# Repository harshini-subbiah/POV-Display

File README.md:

#  POV-Display
Persistence of Vision (POV) is an optical phenomenon where an image remains on the retina for a short time even after the object is no longer visible.
This project implements a POV Display using an Arduino Nano and a rotating set of LEDs. By leveraging the phenomenon where an image remains on the retina for ~1/16th of a second, it creates the illusion of characters or symbols floating in the air.

---
#  Hardware Required
Arduino Nano

1000 RPM DC Motor

5mm Red LEDs

220Ω Resistors

1K Ω Resistors

2K Ω Resistors

IR Sensor

Bluetooth Module (HC-05)

12V Battery

9V Battery

General Purpose Board

Jumper Wires

Hylam Sheet

Zip Ties

Soldering Iron & Wire

---
#  Software Required
1.Arduino IDE to run Code.ino file

2.Serial Bluetooth Terminal app for Bluetooth module

---
#  Setup
1.Follow the circuit diagram and make the proper connections of all the components.

2.Load the Code.ino file to the Nano.

3.Connect the Bluetooth module to the app. It will appear as HC-05 and the password will either be 1234 or 0000.

---
# Circuit Diagram

---

#  Contributors
1. S Harini 

2. Kiran Sampath 

3. Krithikesh

---
# Mentors
1. Mr.Suresh Sir
2. Mr.Vijaykumar Sir

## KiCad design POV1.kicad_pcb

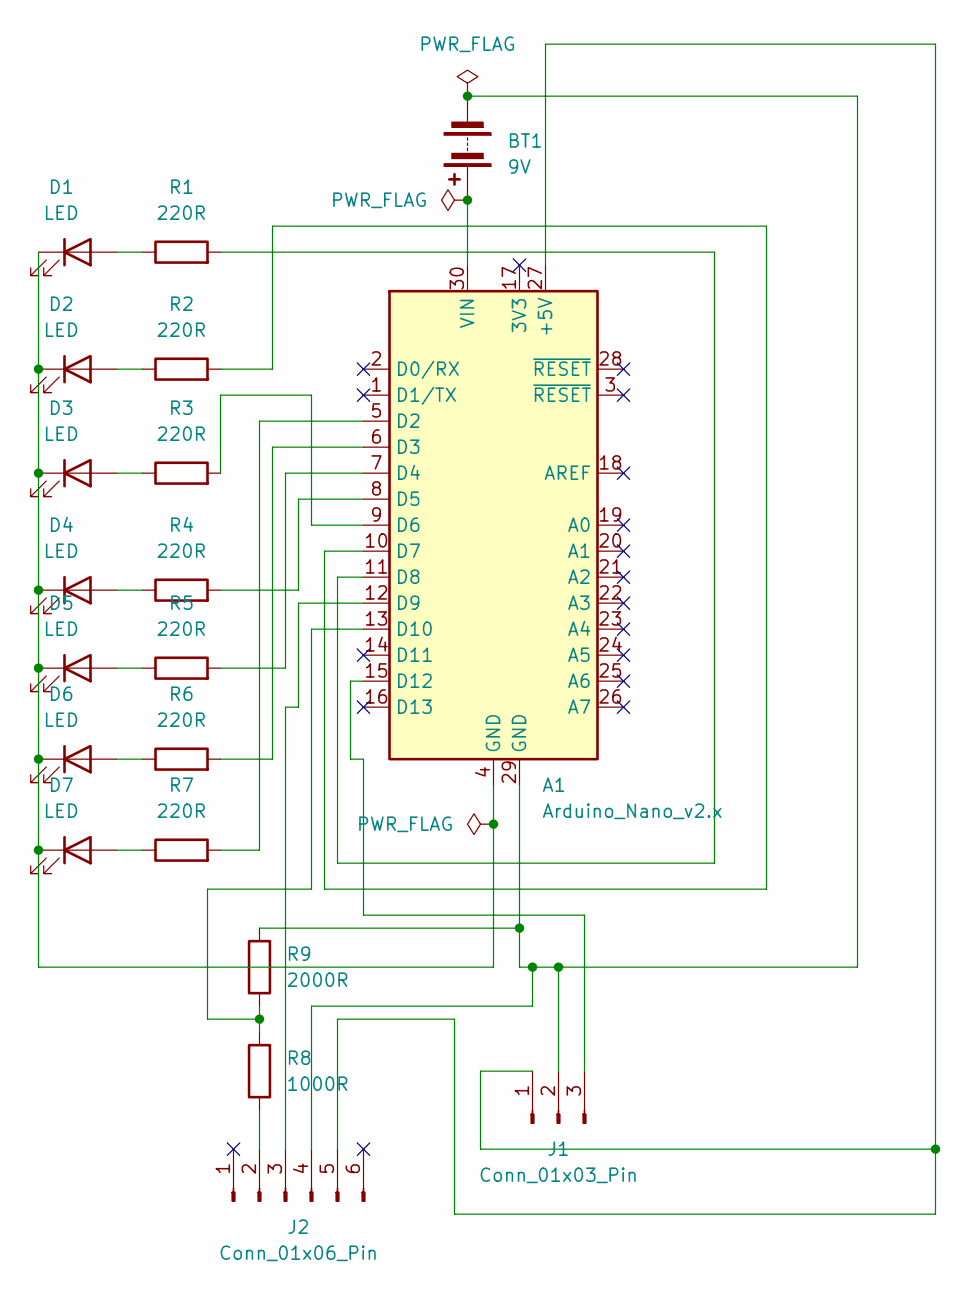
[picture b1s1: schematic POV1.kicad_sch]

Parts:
A1: Arduino_Nano_v2.x; Arduino_Nano
BT1: 9V; BatteryHolder_Eagle_12BH611-GR
D1, D2, D3, D4, D5, D6, D7: LED; LED_D5.0mm
J1: Conn_01x03_Pin; PinSocket_1x03_P2.00mm_Horizontal
J2: Conn_01x06_Pin; PinSocket_1x06_P2.00mm_Horizontal
R1, R2, R3, R4, R5, R6, R7: 220R; R_Axial_DIN0204_L3.6mm_D1.6mm_P1.90mm_Vertical
R8: 1000R; R_Axial_DIN0204_L3.6mm_D1.6mm_P1.90mm_Vertical
R9: 2000R; R_Axial_DIN0204_L3.6mm_D1.6mm_P1.90mm_Vertical

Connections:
unnamed: A1.27 (+5V), J1.1, J2.5
unnamed: A1.5 (D2), R7.2
unnamed: A1.6 (D3), R6.2
unnamed: A1.7 (D4), R5.2
unnamed: A1.8 (D5), R4.2
unnamed: A1.9 (D6), R3.2
unnamed: A1.10 (D7), R2.2
unnamed: A1.11 (D8), R1.2
unnamed: A1.12 (D9), J2.3
unnamed: A1.13 (D10), R8.2, R9.1
unnamed: A1.15 (D12), J1.3
unnamed: A1.30 (VIN), BT1.1 (+)
unnamed: A1.29 (GND), BT1.2 (-), J1.2, J2.4, R9.2
unnamed: D1.2 (A), R1.1
unnamed: A1.4 (GND), D1.1 (K), D2.1 (K), D3.1 (K), D4.1 (K), D5.1 (K), D6.1 (K), D7.1 (K)
unnamed: D2.2 (A), R2.1
unnamed: D3.2 (A), R3.1
unnamed: D4.2 (A), R4.1
unnamed: D5.2 (A), R5.1
unnamed: D6.2 (A), R6.1
unnamed: D7.2 (A), R7.1
unnamed: J2.2, R8.1

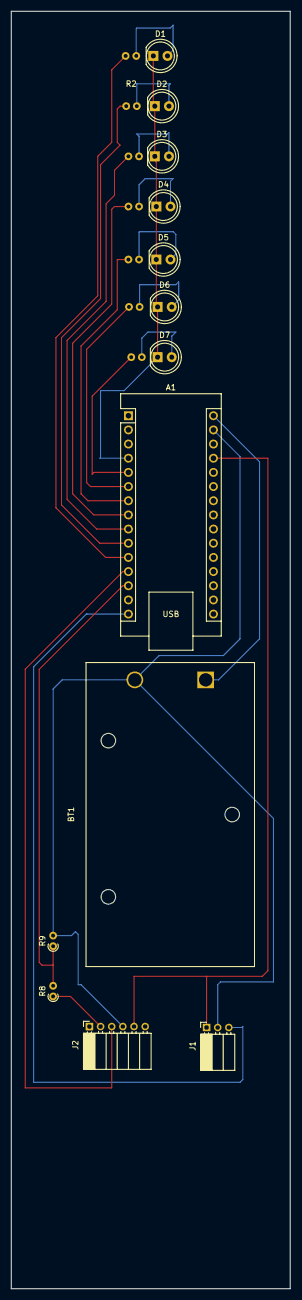
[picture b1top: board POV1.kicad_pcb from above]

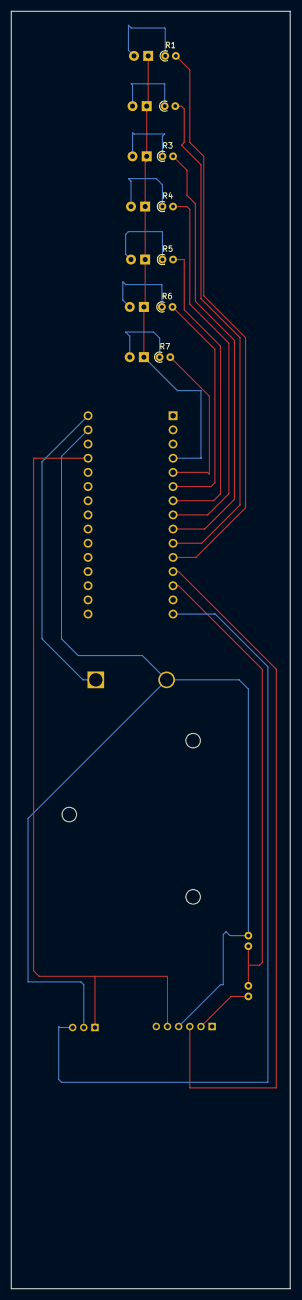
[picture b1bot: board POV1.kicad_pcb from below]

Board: 2 copper layers, 50.0 x 229.0 mm, 20 parts (7 on the bottom side), 22 nets.

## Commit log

2025-07-01 Version1: 7x7 Bitmapping without IR Sensor
2025-07-01 Version2: 7x7 with IR sensor
2025-07-01 Version3: 7x7 with Serial Communication
2025-07-01 Version4: 4x7 with Transpose Function
    Letter Width is changed to 4 and the bitmapping of the letters have been changed and a transpose function has been Included
2025-07-01 Version5: 5x7 with Transpose Function
    Letter Width is changed to 5 and Column Delay to 1ms as well as the bitmapping of letters to 5x7
2025-07-01 Version6: 5x7 with Bluetooth module
    instead of serial communication or inbuilt word to display word it is connected to bluetooth module
